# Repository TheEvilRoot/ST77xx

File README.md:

# ST77xx

Reverse engineering of ST7735/ST7789 breakout board for SPI TFT display.

J1 (Pins) is breakout connector.

DS1 is display flex connector (0.7mm pitch, 0.4x3mm pads)

> Regulator is for 5V compatibility and could be omitted on 3.3V boards.

Connector symbols and footprints are available in library in repository

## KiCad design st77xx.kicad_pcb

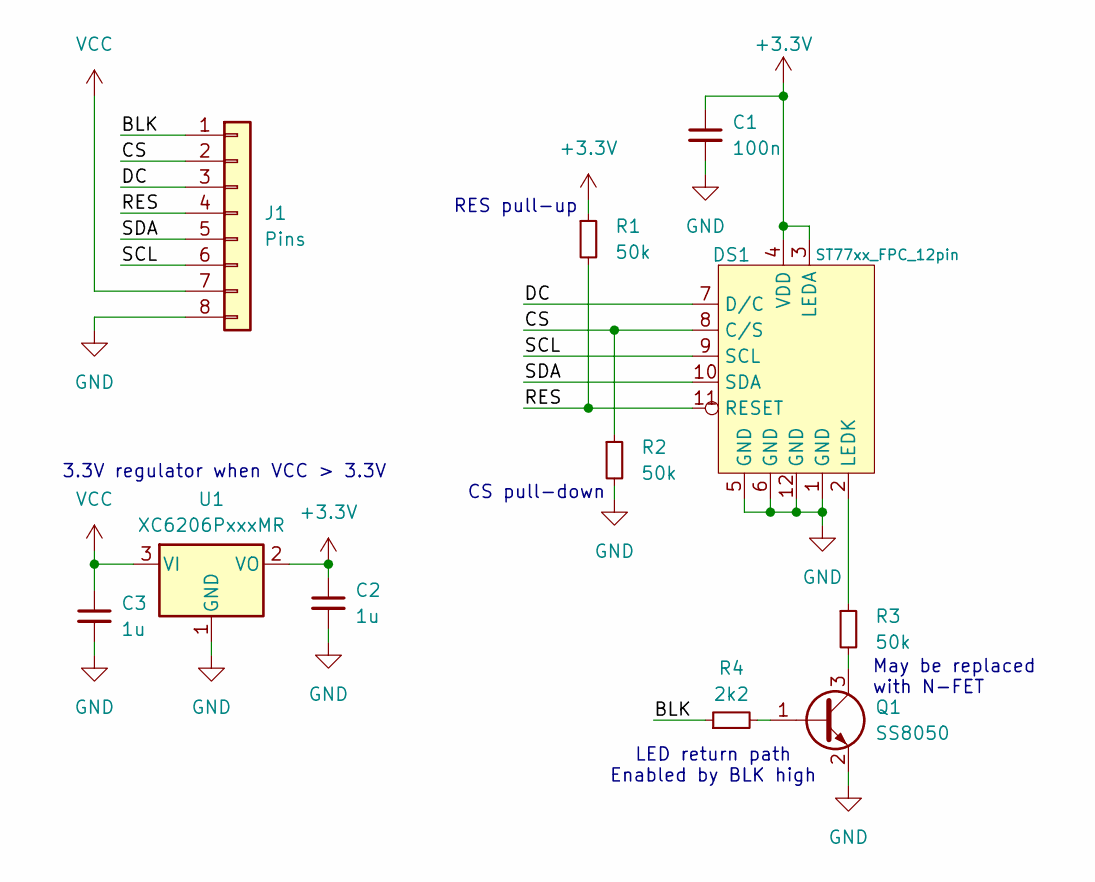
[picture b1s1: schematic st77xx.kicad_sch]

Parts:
C1: 100n; C_0603_1608Metric
C2, C3: 1u; C_0603_1608Metric
DS1: ST77xx_FPC_12pin; ST77XX_FPC_12pin_0.8mm_Solder
J1: Pins; PinHeader_1x08_P2.54mm_Vertical
Q1: SS8050; SOT-23
R1, R2, R3: 50k; R_0603_1608Metric
R4: 2k2; R_0603_1608Metric
U1: XC6206PxxxMR; SOT-23-3

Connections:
+3.3V: C1.1, C2.1, DS1.3 (LEDA), DS1.4 (VDD), R1.1, U1.2 (VO)
/BLK: J1.1, R4.1
/CS: DS1.8 (C/S), J1.2, R2.1
/DC: DS1.7 (D/C), J1.3
/RES: DS1.11 (RESET), J1.4, R1.2
/SCL: DS1.9 (SCL), J1.6
/SDA: DS1.10 (SDA), J1.5
GND: C1.2, C2.2, C3.2, DS1.1 (GND), DS1.5 (GND), DS1.6 (GND), DS1.12 (GND), J1.8, Q1.2 (E), R2.2, U1.1 (GND)
unnamed: DS1.2 (LEDK), R3.1
unnamed: Q1.1 (B), R4.2
unnamed: Q1.3 (C), R3.2
VCC: C3.1, J1.7, U1.3 (VI)

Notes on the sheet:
RES pull-up
LED return path Enabled by BLK high
May be replaced with N-FET
CS pull-down
3.3V regulator when VCC > 3.3V

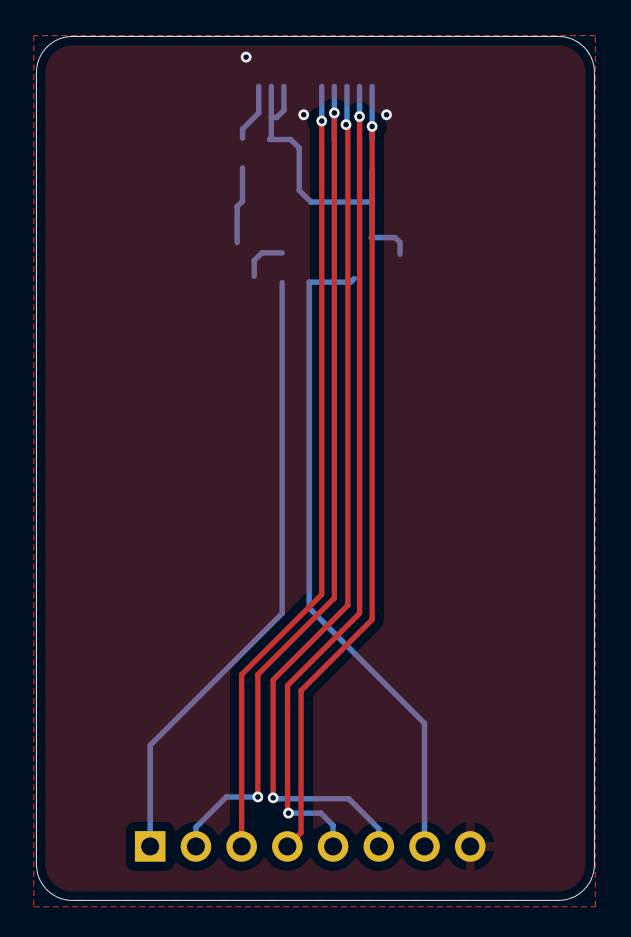
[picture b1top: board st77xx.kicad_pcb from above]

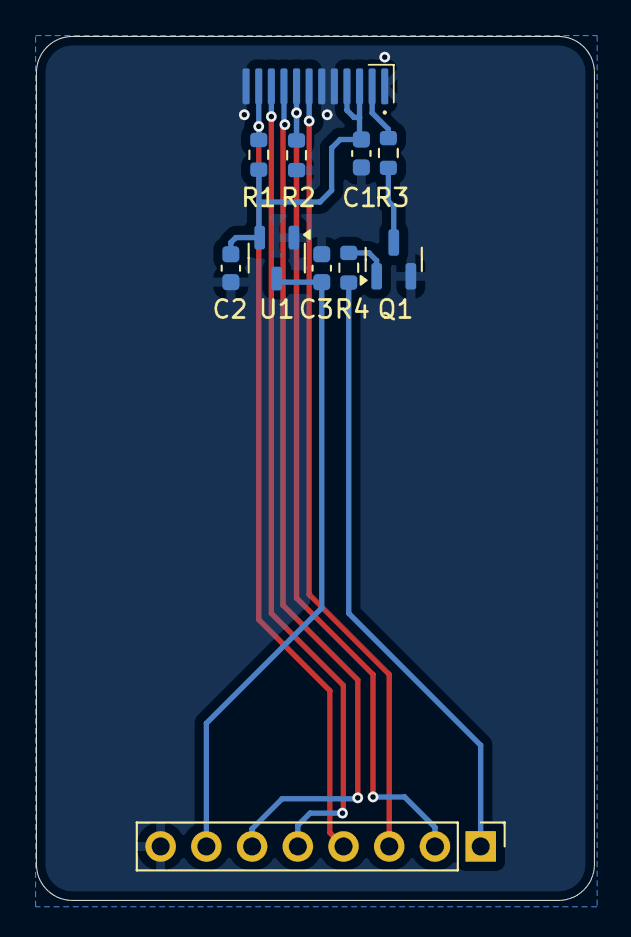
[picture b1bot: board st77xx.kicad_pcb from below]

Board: 2 copper layers, 31.0 x 48.0 mm, 11 parts (11 on the bottom side), 12 nets.

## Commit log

2024-12-16 Initial
2025-01-29 Fix schematic
2025-03-24 Remove DS_Store
2025-03-24 Fix LEDK resistor
